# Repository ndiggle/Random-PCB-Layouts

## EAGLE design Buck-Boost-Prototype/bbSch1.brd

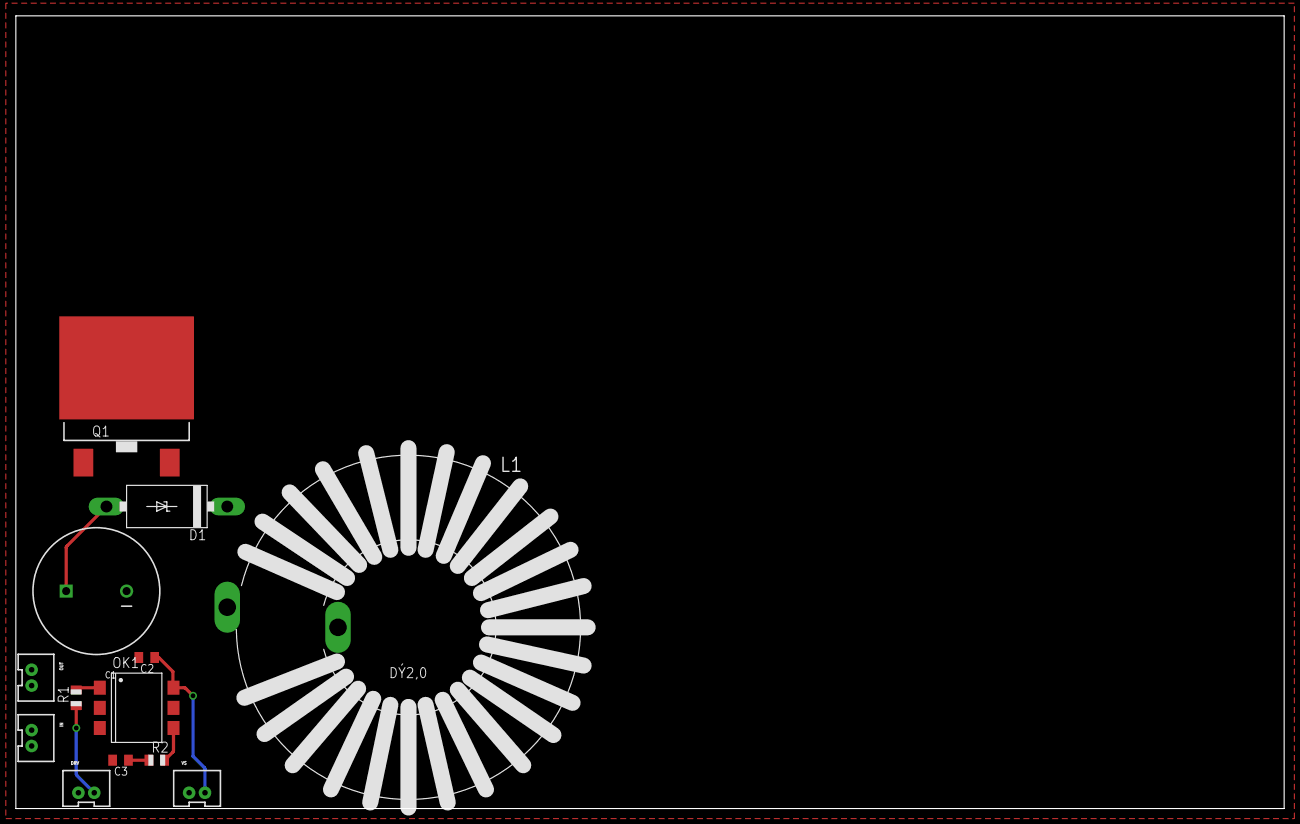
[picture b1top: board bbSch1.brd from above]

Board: 2 copper layers, 160.0 x 100.0 mm, 13 parts (0 on the bottom side), 9 nets.

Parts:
C1: 2000uF; CPOL-RADIAL-1000UF-63V
C2: 0.1uF; C0805K
C3: 10nF; C0805K
D1: C4111-15
DRV: JST-2-PTH-VERT
IN: JST-2-PTH-VERT
L1: 2700uH; RKE10
OK1: H11L1MS; DIL6-SMD
OUT: JST-2-PTH-VERT
Q1: IXGT6N170; TO268
R1: 1.6k; R0805
R2: 10; R0805
VS: JST-2-PTH-VERT

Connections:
+18V: C2.1, OK1.6, VS.2
GND: C1.2, C2.2, C3.2, DRV.1, IN.1, L1.2, OK1.2, OK1.5, OUT.1, VS.1
unnamed: OK1.1, R1.2
unnamed: D1.C, L1.1, Q1.E
unnamed: C3.1, R2.1
VDRIVE: DRV.2, R1.1
VDRIVE18: OK1.4, Q1.G, R2.2
VIN: IN.2, Q1.C@1, Q1.C@2
VOUT: C1.1, D1.A, OUT.2

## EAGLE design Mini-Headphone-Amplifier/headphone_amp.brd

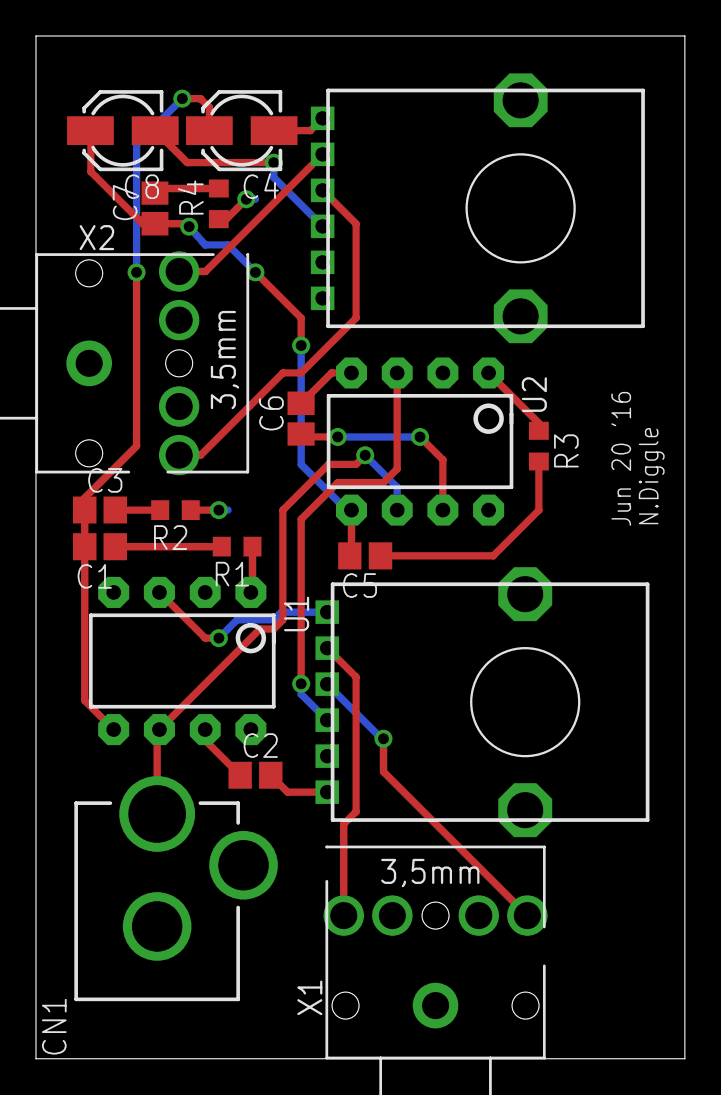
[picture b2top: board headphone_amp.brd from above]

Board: 2 copper layers, 36.0 x 56.8 mm, 19 parts (0 on the bottom side), 20 nets.

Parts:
C1, C2, C3, C5, C6, C7: C0805
C4, C8: 153CLV-0405
CN1: DCJACK_2MM_PTH
R1, R2, R3, R4: R0603
RV1, RV2: POT_PANASONIC_DUAL_VERT
U1, U2: LM386; DIP08
X1, X2: STEREOJACK; STX3100

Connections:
GND: C2.2, C6.2, CN1.GND, CN1.GNDBREAK, R2.1, R4.1, RV1.A3, RV1.B3, RV2.A3, RV2.B3, U1.2, U1.4, U2.2, U2.4, X1.1, X2.1
IN_L: RV1.A1, X1.2
IN_R: RV1.B1, X1.5
unnamed: C2.1, U1.7
unnamed: RV1.A2, U1.3
unnamed: R1.1, U1.1
unnamed: C1.1, R1.2
unnamed: C1.2, C3.1, C4.+, U1.5
unnamed: C3.2, R2.2
unnamed: C4.-, RV2.A2
unnamed: R3.1, U2.1
unnamed: RV1.B2, U2.3
unnamed: C5.1, R3.2
unnamed: C5.2, C7.1, C8.+, U2.5
unnamed: C6.1, U2.7
unnamed: C7.2, R4.2
unnamed: C8.-, RV2.B2
OUT_L: RV2.A1, X2.2
OUT_R: RV2.B1, X2.5
VCC: CN1.PWR, U1.6, U2.6

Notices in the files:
parts and their libraries:
SparkFun-Passives: Licensing: Creative Commons ShareAlike 4.0 International - https://creativecommons.org/licenses/by-sa/4.0
